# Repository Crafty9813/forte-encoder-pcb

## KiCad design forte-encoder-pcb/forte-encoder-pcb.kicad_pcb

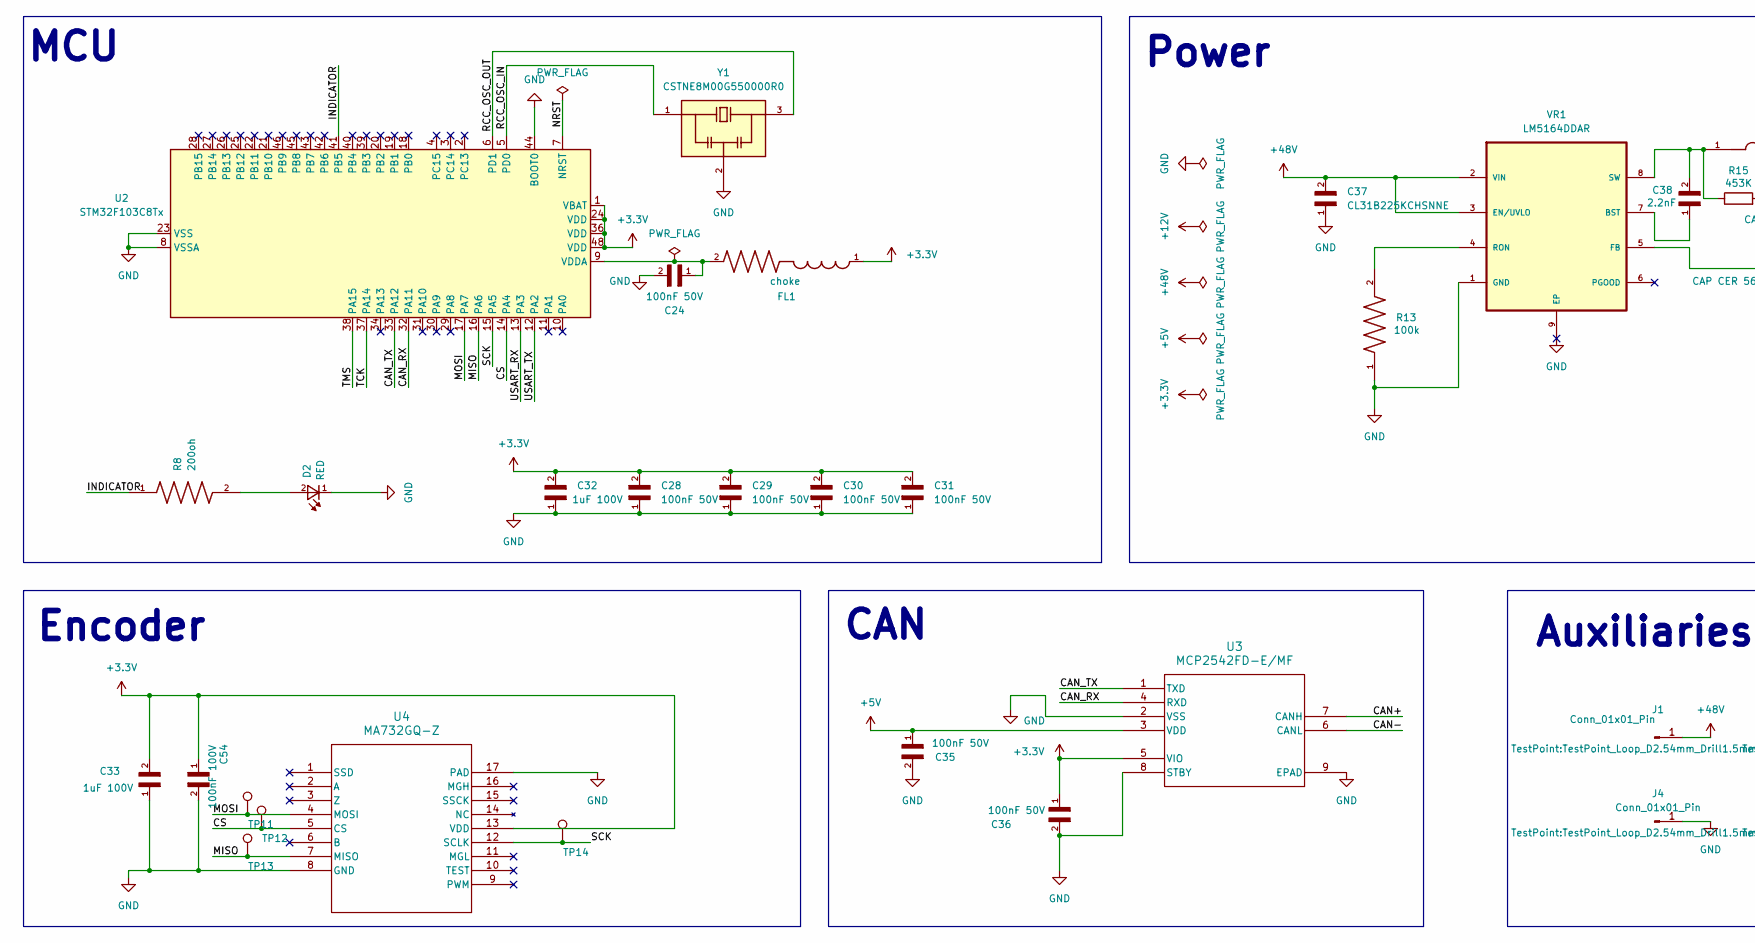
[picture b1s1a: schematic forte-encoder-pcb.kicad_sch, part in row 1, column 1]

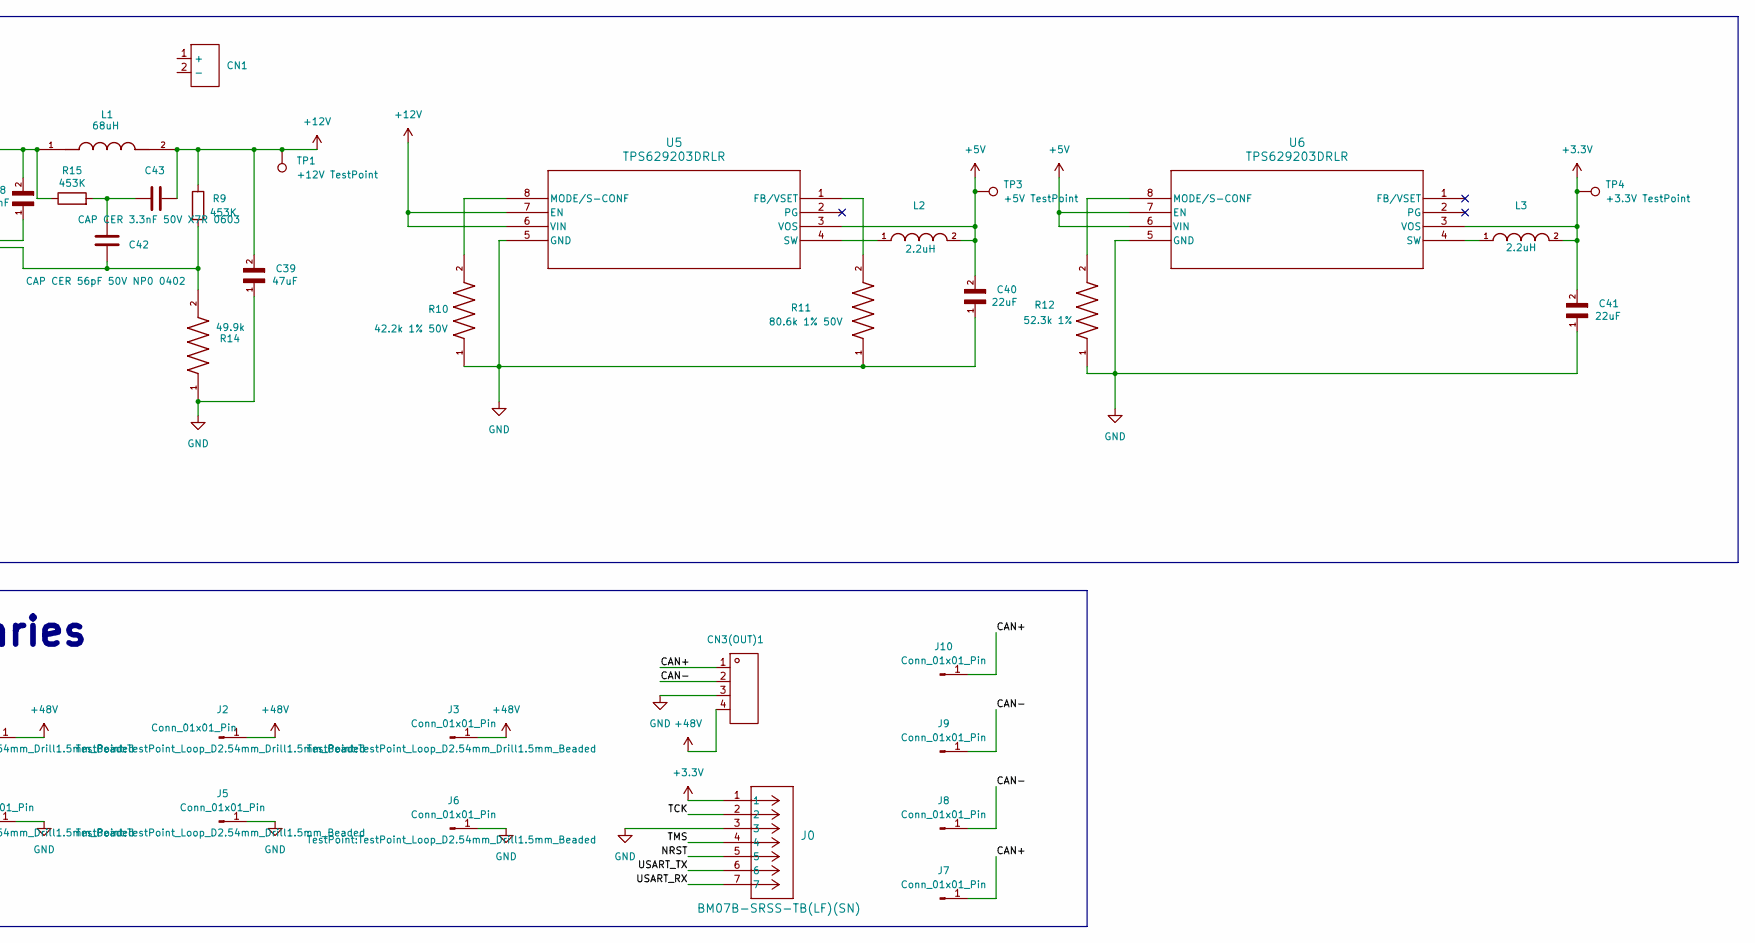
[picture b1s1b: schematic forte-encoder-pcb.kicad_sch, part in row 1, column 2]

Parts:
C24, C28, C29, C30, C31, C35, C36: 100nF 50V; CC0603JRX7R9BB104
C32: CL31B105KCHNNNE
C33: 1uF 100V; GRM21BC72A105KE01L
C37: CL31B225KCHSNNE
C38: CL10B222KB8NNNC
C39: GRM31CR61E476ME44L
C40, C41: GRM32ER71E226KE15L
C42: CC0402JRNPO9BN560; RC0402FR_0752K3L
C43: Samsung Electro-Mechanics CL10B332KB8NNNC; CC0603JRX7R9BB104
C54: 100nF 100V; CL10B104KC8NNNC
CN1: CONN-TH_XT30UPB-F; Manufacturer Part XT30UPB-F30.G.Y
CN3(OUT)1: XT30(2+2)PB-M.G.B; Manufacturer Part XT30(2+2)PB-M.G.B
D2: LITEON LTST-C191KRKT; LTST_C191KRKT
FL1: BLM18AG601SN1D
J0: BM07B-SRSS-TB(LF)(SN); BM07B-SRSS-TB
J1, J2, J3, J4, J5, J6: Conn_01x01_Pin; TestPoint_Loop_D2.54mm_Drill1.5mm_Beaded
J7, J8, J9, J10: Conn_01x01_Pin; TestPoint_THTPad_D1.5mm_Drill0.7mm
L1: TDK VLS5045EX-680M; VLS5045EX_680M; PARTREV N/A
L2, L3: DFE252012PD-2R2M=P2; DFE252012PD_2R2M_P2
R8: 200oh; RC0402JR-07200RL
R9, R15: 0603WAF4533T5E; RT0603BRD07448KL
R10: RC0402FR-0742K2L; RC0402FR_0742K2L
R11: RC0402FR-0780K6L; RC0402FR_0780K6L
R12: RC0402FR-0752K3L; RC0402FR_0752K3L
R13: RC0805FR-07100KL; RC0805FR_07100KL
R14: RT0603BRD0749K9L
TP1: +12V TestPoint; TestPoint_Pad_D1.5mm
TP3: +5V TestPoint; TestPoint_Pad_D1.5mm
TP4: +3.3V TestPoint; TestPoint_Pad_D1.5mm
TP11: TP_MOSI; TestPoint_Pad_D1.0mm
TP12: TP_CS; TestPoint_Pad_D1.0mm
TP13: TP_MISO; TestPoint_Pad_D1.0mm
TP14: TP_SCK; TestPoint_Pad_D1.0mm
U2: STM32F103C8Tx; LQFP-48_7x7mm_P0.5mm
U3: MCP2542FD-E/MF; MCP2542FD_E_MF
U4: MA732GQ-Z
U5, U6: TPS629203DRLR
VR1: LM5164DDAR
Y1: CSTNE8M00G550000R0

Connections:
+3.3V: C28.2, C29.2, C30.2, C31.2, C32.2, C33.2, C36.1, C41.2, C54.1, FL1.1, J0.1, L3.2, TP4.1 (1_1), U2.1 (VBAT), U2.24 (VDD), U2.36 (VDD), U2.48 (VDD), U3.5 (VIO), U4.13 (VDD), U6.3 (VOS)
+5V: C35.1, C40.2, L2.2, TP3.1 (1_1), U3.3 (VDD), U5.3 (VOS), U6.6 (VIN), U6.7 (EN)
+12V: C39.2, C43.2, L1.2, R9.1, TP1.1 (1_1), U5.6 (VIN), U5.7 (EN)
+48V: C37.2, CN3(OUT)1.4, J1.1 (Pin_1_1), J2.1 (Pin_1_1), J3.1 (Pin_1_1), VR1.2 (VIN), VR1.3 (EN/UVLO)
/CAN+: CN3(OUT)1.1, J7.1 (Pin_1_1), J10.1 (Pin_1_1), U3.7 (CANH)
/CAN-: CN3(OUT)1.2, J8.1 (Pin_1_1), J9.1 (Pin_1_1), U3.6 (CANL)
/CAN_RX: U2.32 (PA11), U3.4 (RXD)
/CAN_TX: U2.33 (PA12), U3.1 (TXD)
/CS: TP12.1 (1_1), U2.14 (PA4), U4.5 (CS)
/INDICATOR: R8.1, U2.41 (PB5)
/MISO: TP13.1 (1_1), U2.16 (PA6), U4.7 (MISO)
/MOSI: TP11.1 (1_1), U2.17 (PA7), U4.4 (MOSI)
/NRST: J0.5, U2.7 (NRST)
/RCC_OSC_IN: U2.5 (PD0), Y1.1
/RCC_OSC_OUT: U2.6 (PD1), Y1.3
/SCK: TP14.1 (1_1), U2.15 (PA5), U4.12 (SCLK)
/TCK: J0.2, U2.37 (PA14)
/TMS: J0.4, U2.38 (PA15)
/USART_RX: J0.7, U2.13 (PA3)
/USART_TX: J0.6, U2.12 (PA2)
GND: C24.2, C28.1, C29.1, C30.1, C31.1, C32.1, C33.1, C35.2, C36.2, C37.1, C39.1, C40.1, C41.1, C54.2, CN3(OUT)1.3, D2.1, J0.3, J4.1 (Pin_1_1), J5.1 (Pin_1_1), J6.1 (Pin_1_1), R10.1, R11.1, R12.1, R13.1, R14.1, U2.8 (VSSA), U2.23 (VSS), U2.35 (VSS), U2.44 (BOOT0), U2.47 (VSS), U3.2 (VSS), U3.8 (STBY), U3.9 (EPAD), U4.8 (GND), U4.17 (PAD), U5.5 (GND), U6.5 (GND), VR1.1 (GND), VR1.9 (EP), Y1.2
unnamed: C42.1, C43.1, R15.2
unnamed: D2.2, R8.2
unnamed: C24.1, FL1.2, U2.9 (VDDA)
unnamed: R11.2, U5.1 (FB/VSET)
unnamed: R10.2, U5.8 (MODE/S-CONF)
unnamed: L2.1, U5.4 (SW)
unnamed: R12.2, U6.8 (MODE/S-CONF)
unnamed: L3.1, U6.4 (SW)
unnamed: C38.1, VR1.7 (BST)
unnamed: C42.2, R9.2, R14.2, VR1.5 (FB)
unnamed: R13.2, VR1.4 (RON)
unnamed: C38.2, L1.1, R15.1, VR1.8 (SW)

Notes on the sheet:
MCU
Encoder
Auxiliaries
CAN
Power

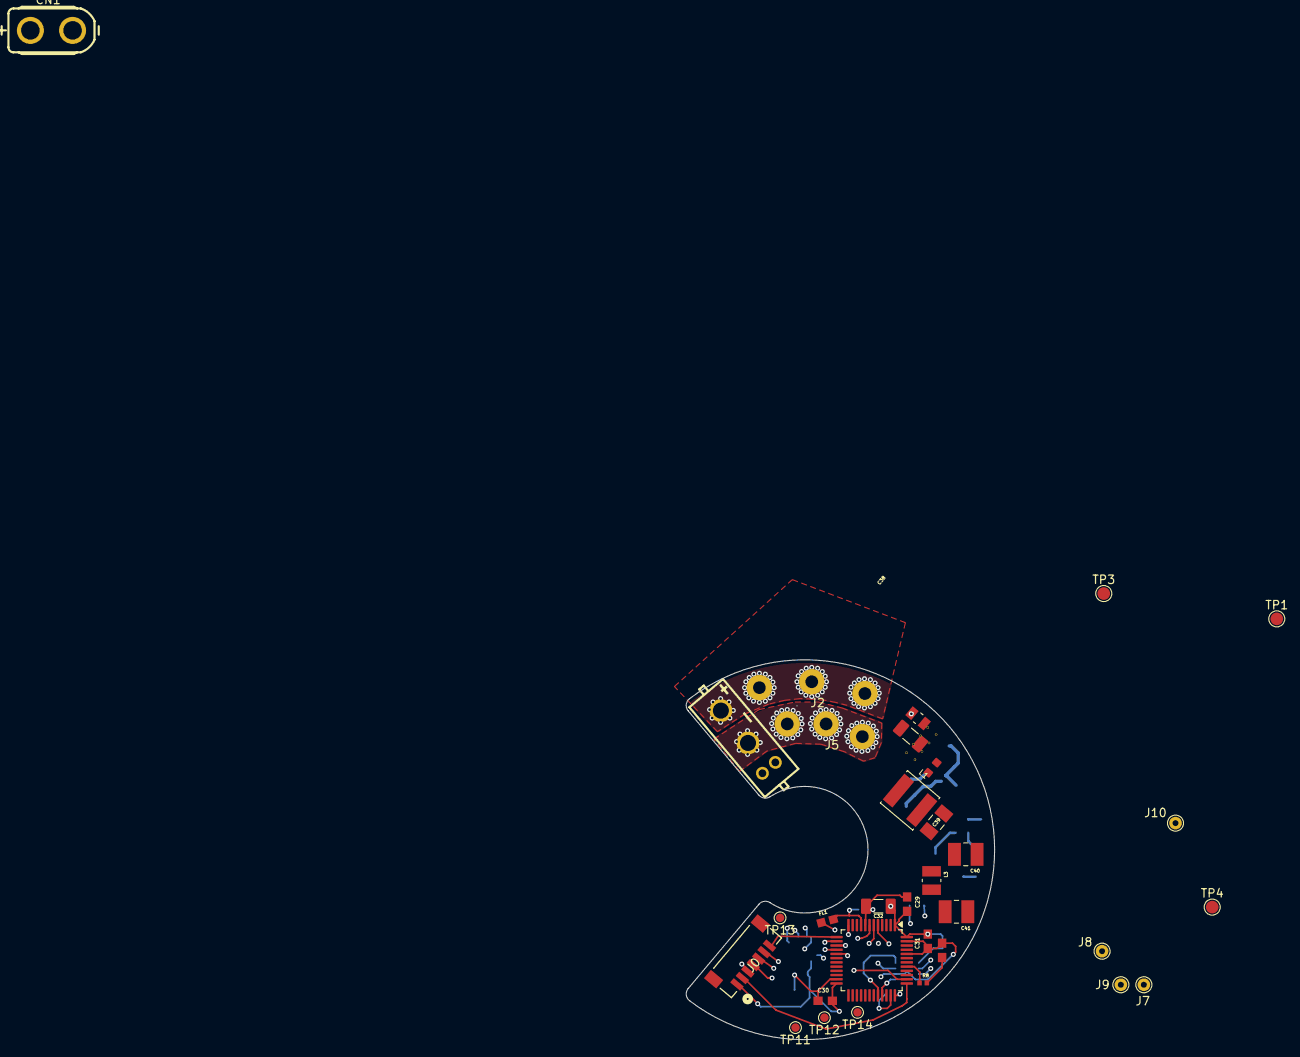
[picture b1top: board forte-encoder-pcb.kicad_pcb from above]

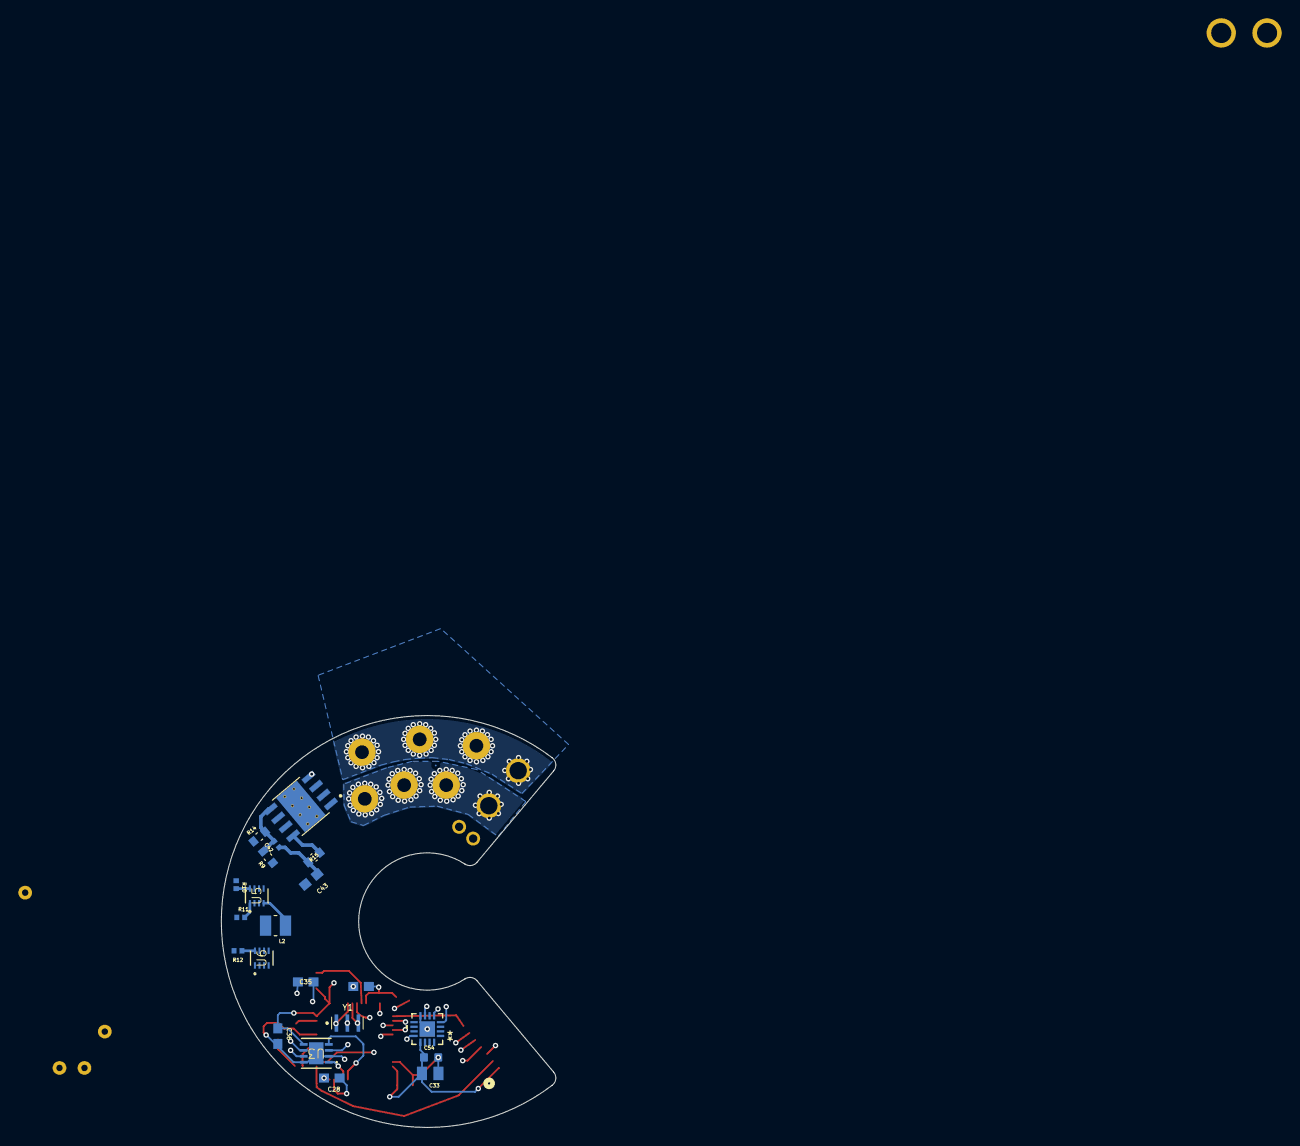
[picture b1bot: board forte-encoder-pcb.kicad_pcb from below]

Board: 6 copper layers, 36.5 x 45.0 mm, 57 parts (21 on the bottom side), 33 nets.

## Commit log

2026-04-19 SPI for ma732 and stm32
2026-04-22 halp
2026-04-22 modify pcb
2026-04-23 super messy
2026-04-23 needa double check but "done"
2026-04-23 kcl shouldn't be an issue right...
2026-04-24 Mounting holes
2026-04-24 Add images
2026-05-14 push all changes
